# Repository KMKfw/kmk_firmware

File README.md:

# KMK: Clackety Keyboards Powered by Python

KMK is a feature-rich and beginner-friendly firmware for computer keyboards
written and configured in
[CircuitPython](https://github.com/adafruit/circuitpython).

## Status

KMK is no longer actively maintained and on limited life support.
Issues and pull requests will not be addressed for the time being.
Volunteers for taking on the project can voice their interest in the
[Zulip Chat](https://kmkfw.zulipchat.com).

## Support

For asynchronous support and chatter about KMK, [join our Zulip
community](https://kmkfw.zulipchat.com)!

If you ask for help in chat or open a bug report, if possible
make sure your copy of KMK is up-to-date.
In particular, swing by the Zulip chat *before* opening a GitHub Issue about
configuration, documentation, etc. concerns.

> The former Matrix and Discord rooms once linked to in this README are no
> longer officially supported, please do not use them!

## Features

- Fully configured through a single, easy to understand Python file that lives
  on a "flash-drive"-esque space on your microcontroller - edit on the go
  without DFU or other dev tooling available!
- Single-piece or [two-piece split
  keyboards](/docs/en/split_keyboards.md)
  are supported
- [Chainable
  keys](/docs/en/keys.md) such as
  `KC.LWIN(KC.L)` to lock the screen on a Windows PC
- [Built-in Unicode macros, including
  emojis](/docs/en/macros.md)
- [RGB underglow](/docs/en/rgb.md)
  and [LED
  backlights](/docs/en/led.md)
- One key can turn into many more based on [how many times you tap
  it](/docs/en/tapdance.md)
- Bluetooth HID and split keyboards. No more wires.

## Getting Started

KMK requires [CircuitPython](https://circuitpython.org/) version 8.0 or higher.
Our getting started guide can be found
[here](/docs/en/Getting_Started.md).

## Contributing

Please have a look at the [contributing document](/docs/en/contributing.md), 
where you can find details about the workflow and code style. If you have 
specific questions feel free to ask in the [KMK development stream](https://kmkfw.zulipchat.com/#narrow/stream/384078-KMK-development) 
on Zulip.

## License, Copyright, and Legal

All software in this repository is licensed under the [GNU Public License,
version 3](https://tldrlegal.com/license/gnu-general-public-license-v3-(gpl-3)).
All documentation and hardware designs are licensed under the [Creative Commons
Attribution-ShareAlike 4.0](https://creativecommons.org/licenses/by-sa/4.0/)
license.

**Due to ethical and legal concerns, any works derived from GitHub Copilot or
similar artificial intelligence tooling are unacceptable for inclusion in any
first-party KMK repository or other code collection. We further recommend not
using GitHub Copilot while developing anything KMK-related, regardless of
intent to submit upstream.**

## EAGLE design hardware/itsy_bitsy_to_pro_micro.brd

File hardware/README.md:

# KMK Hardware: Devices for use with KMK

## ItsyBitsy to Pro Micro pinout adapter

This board adapts the pinout of a Circuit Python compatible [Adafruit ItsyBitsy M4 Express](https://www.adafruit.com/product/3800) to that of the [SparkFun Pro Micro](https://www.sparkfun.com/products/12640) to allow the ItsyBitsy to be used with the many keyboards that support the footprint of the Pro Micro.

## Pin mapping
| Pro Micro Pin   | ItsyBitsy Pin   |
|-----------------|-----------------|
| `TX0/PD3`       | `TX`            |
| `RX1/PD2`       | `RX`            |
| `GND`           | `GND`           |
| `GND`           | `GND`           |
| `2/PD1`         | `SDA`           |
| `3/PD0`         | `SCL`           |
| `4/PD4`         | `D13`           |
| `5/PC6`         | `D12`           |
| `6/PD7`         | `D11`           |
| `7/PE6`         | `D10`           |
| `8/PB4`         | `D9`            |
| `9/PB5`         | `D7`            |
| `Raw`           |                 |
| `GND`           | `GND`           |
| `RST`           | `RST`           |
| `VCC`           | `USB`           |
| `A3/PF4`        | `A0`            |
| `A2/PF5`        | `A1`            |
| `A1/PF6`        | `A2`            |
| `A0/PF7`        | `A3`            |
| `15/PB1`        | `A4`            |
| `14/PB3`        | `A5`            |
| `16/PB2`        | `SCK`           |

## So how do I use it?
1. The pads for the Pro Micro footprint are circled on the underside of the board. Solder male headers into these pads on the underside of the board (the same side as the markings) so that the pins extend "downward" so that they can be plugged into the keyboard.

2. The remaining pads are for the ItsyBitsy. Assuming height is a concern, rather than soldering male headers into the ItsyBitsy and female headers into the adapter board, instead place the long side of male headers through the ItsyBitsy pads from underneath the board so that they protrude through he pads on the top of the board and solder them in place. Make sure to keep the headers perpendicular to the surface of the board.

3. Once soldered, place the ItsyBitsy board over the headers that are now protruding upwards so that the headers go through the pads of the ItsyBitsy and solder in place.

4. Trim the ItsyBitsy headers as needed with flush cutters.

## License, Copyright, and Legal

The files in this directory are licensed 
[CC BY-SA 4.0](https://tldrlegal.com/license/creative-commons-attribution-sharealike-4.0-international-(cc-by-sa-4.0))
while the TL;DR is linked, the full license text is included in `LICENSE.md` in this directory.

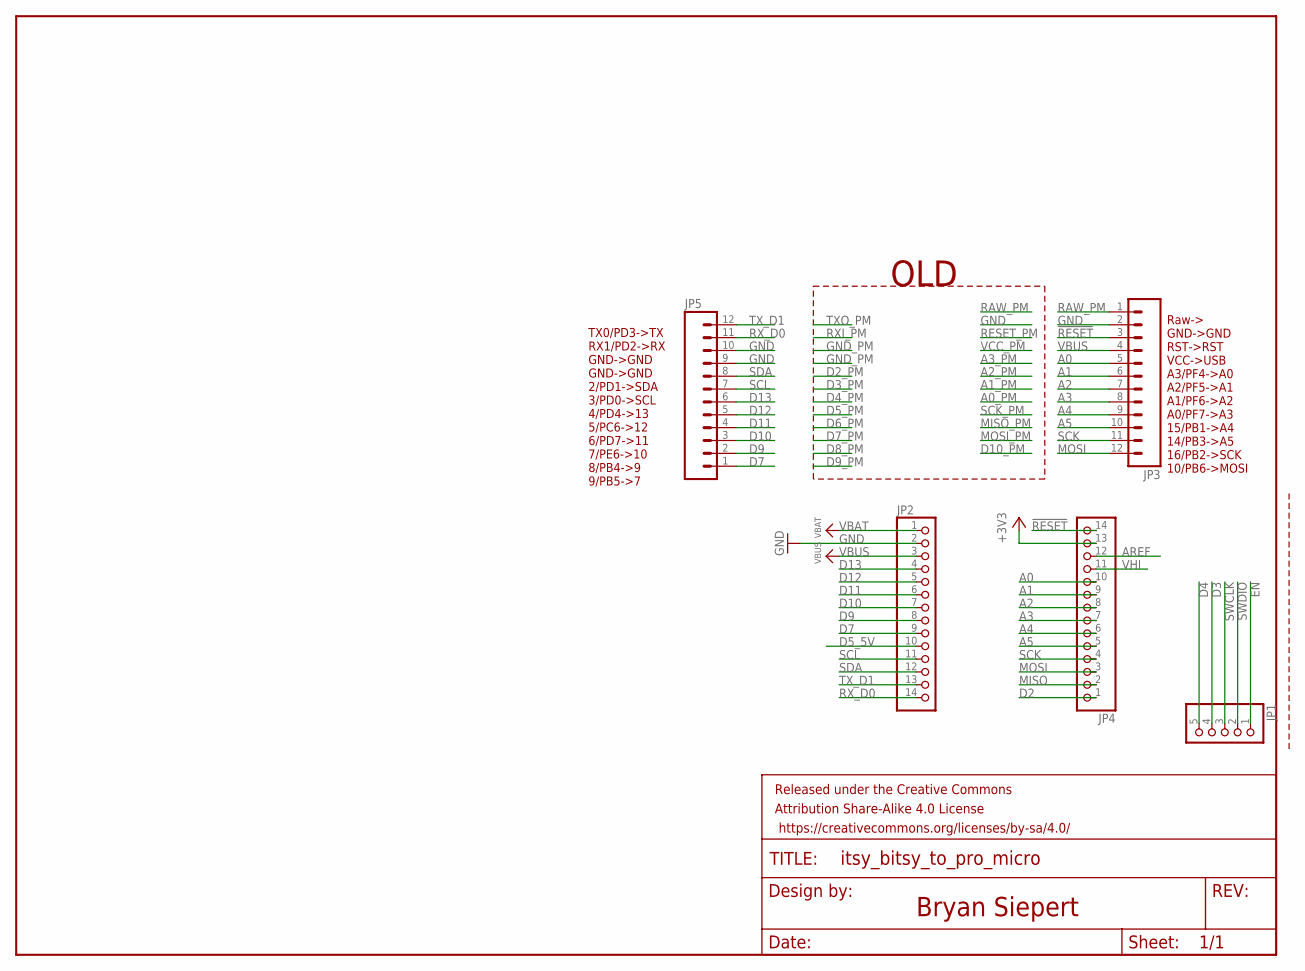
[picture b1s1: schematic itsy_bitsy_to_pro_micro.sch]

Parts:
FRAME2: FRAME-LETTER; CREATIVE_COMMONS
JP1: HEADER-1X570MIL; 1X05_ROUND_70
JP2, JP4: HEADER-1X14; 1X14_ROUND70
JP3, JP5: M12PTH; 1X12

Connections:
!RESET: JP3.3, JP4.14
+3V3: JP4.13
A0: JP3.5, JP4.10
A1: JP3.6, JP4.9
A2: JP3.7, JP4.8
A3: JP3.8, JP4.7
A4: JP3.9, JP4.6
A5: JP3.10, JP4.5
AREF: JP4.12
D2: JP4.1
D3: JP1.4
D4: JP1.5
D5_5V: JP2.10
D7: JP2.9, JP5.1
D9: JP2.8, JP5.2
D10: JP2.7, JP5.3
D11: JP2.6, JP5.4
D12: JP2.5, JP5.5
D13: JP2.4, JP5.6
EN: JP1.1
GND: JP2.2, JP3.2, JP5.9, JP5.10
MISO: JP4.2
MOSI: JP3.12, JP4.3
RAW_PM: JP3.1
RX_D0: JP2.14, JP5.11
SCK: JP3.11, JP4.4
SCL: JP2.11, JP5.7
SDA: JP2.12, JP5.8
SWCLK: JP1.3
SWDIO: JP1.2
TX_D1: JP2.13, JP5.12
VBAT: JP2.1
VBUS: JP2.3, JP3.4
VHI: JP4.11

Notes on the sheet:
TX0/PD3->TX RX1/PD2->RX GND->GND GND->GND 2/PD1->SDA 3/PD0->SCL 4/PD4->13 5/PC6->12 6/PD7->11 7/PE6->10 8/PB4->9 9/PB5->7
OLD
Raw-> GND->GND RST->RST VCC->USB A3/PF4->A0 A2/PF5->A1 A1/PF6->A2 A0/PF7->A3 15/PB1->A4 14/PB3->A5 16/PB2->SCK 10/PB6->MOSI
Bryan Siepert

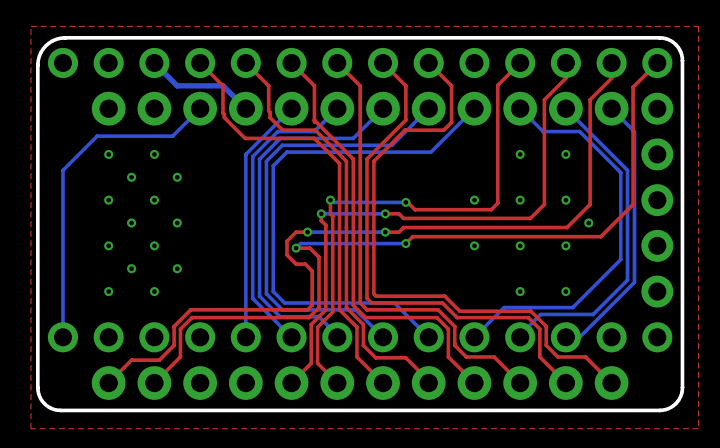
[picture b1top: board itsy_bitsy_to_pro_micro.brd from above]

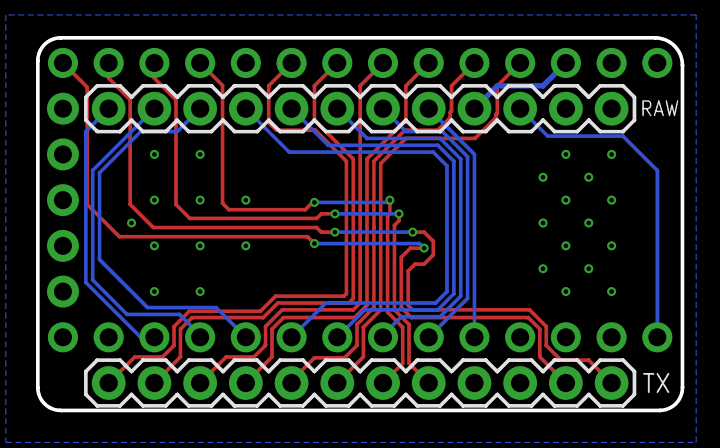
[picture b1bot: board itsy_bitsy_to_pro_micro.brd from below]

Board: 2 copper layers, 35.8 x 20.7 mm, 6 parts (2 on the bottom side), 21 nets.

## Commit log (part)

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2024-07-26 Update pimoroni_trackball.py
    Change variable names
2024-07-29 Fix runtime removal of failed extensions
2024-07-31 removed duplicate newline
2024-07-31 line length linting
2024-08-15 Fix kana check in lock_status.py
2024-08-15 Fix typo in combo_layers.md (#1017)
    changes KC.8 to KC.N8
    fixes a minor typo in the example
2024-08-20 Add docs for pimoroni trackball handlers (#1020)
2024-08-28 Fixed grammatical mistakes, added clarification (#1022)
    When I first wrote this doc, I made a ton of mistakes. Came back to it to clean it up a bit and it should make more sense now.
2024-08-31 Fix formatting
    make black happy
2024-08-31 Fix spelling in oneshot.md
2024-09-03 Refactor RapidFire
    * Fix RapidFireKey argument expansion
    * Add basic unit test
    * Fix calling keyboard.tap() from within a scheduled task
    * Simplify code and memory management
2024-09-03 Fix dependency of TapDance on instantiated HoldTap
2024-09-19 International keys didn't work (#1029)
    * Update international.py
    Fixes the International Keys
    ---------
2024-09-20 Use includes instead of excludes for black
2024-09-23 Keep spellcheck from searching hidden directories.
    Otherwise spellcheck will search for example in `.venv` for typos in
    tooling packages. Maybe the search expression should be a positive list.
2024-10-08 Refactor venv (#1031)
    * Merge setup.cfg into pyproject.toml
    * Use includes instead of excludes for black
    * Remove pipenv dependency
    * Keep spellcheck from searching hidden directories.
    Otherwise spellcheck will search for example in `.venv` for typos in
    tooling packages. Maybe the search expression should be a positive list.
2024-10-17 Add documentation for custom keys
2024-10-19 Fix an error in rgb.md
2024-10-21 Fix key class in international.py
2024-10-21 Fix key class in international.py (#1038)
    * Fix key class in international.py
    * fixup
2024-11-04 Minor tweaks to the example in the Display extension doc (#926)
    Minor tweaks to the Display extension doc
2024-11-04 flip layout (one handed typing)
2024-11-04 Removed intify_coordinate from code, boards, docs (#924)
    Remove deprecated intify_coordinate mapping
2024-11-04 Fix spelling (#920)
    Fix spelling
2024-11-04 undebug
2024-11-04 clean up (a little)
2024-11-04 minor doc updates
2024-11-05 Add TGS command to toggle between active layers
2024-11-07 Expose it in other scanners as well
2024-11-07 Even saner defaults
2024-11-07 Lint
2024-11-07 Lint III
2024-11-08 Catching all them arguments
2024-11-08 Allow passing debounce_threshold in keypad.py (#1044)
    * Expose debounce_threshold in keypad.py
2024-11-10 Add __init__() to KMKKeyboard
2024-11-19 Remove OneShot module
2024-11-19 Replace print() with guarded debug()
2024-11-19 Remove KC.DEBUG from keys.py
2024-11-19 Bring back DEBUG key
2024-12-09 Make bootcfg sense optional
    In case we're only interested in non-lockout-prone options, like NKRO
2024-12-09 remove `KC.DEBUG` cleanup
2024-12-10 Implement generalized analog input module
2024-12-11 Fix sticky_keys defer_release
2024-12-14 New unit tests
2024-12-14 Fix sticky_keys hold release (#1055)
    * Fix sticky_keys hold release
    * Update sticky_keys.md
    * Update aspell.en.pws
    * New unit tests
2024-12-15 Fixed and added to docs, changed senstol to sensitivity
    fixed AnalogKeys example, added sensitivity to docs and changed name in code from senstol (tolerance might be better wording not sure..)
    changed analog in examples to analogInputMap to better match up with keymap.py naming for encoders and what-not
    added explanation to AnalogKey example to better explain what it does
2024-12-16 Fix scanners.md
2024-12-16 Appease linter
2024-12-16 Fix scanners.md (#1058)
    * Fix scanners.md
    * Fix affected boards
2024-12-18 add start_watchdog() method
2024-12-18 better naming and neater debug
2024-12-22 remove artifacts
2024-12-23 Fix DiodeOrientation to columns_to_anodes mapping
2024-12-29 made analogio scanner (not mux yet)
    Made AnalogIo scanner that can scan single input.
    muxing should just be adding scanning with shifing the pins on the mux so not to hard but will need to take in muxers as an array in themself so multiple can be supported at once
    this is mostly baised on the Digital Io scanner but I see no exsamples as to where it gets it's offset from.
2024-12-29 changed threshold to threshold_map
    added parcing for a threshhold map and code to fill it with 127's of nothing provided
2025-01-03 boards/anavi/knob1/README.md: Display
    Add information about the Display extension for ANAVI Knob 1.
2025-01-04 boards/anavi/macro-pad-12/README.md: Fix link (#1065)
    Fix the link to the documentation for the display.
2025-01-06 larger rework
    the more I learn the more I "fix"
    this one is mainly wordy with my notes but I've moved a lot of handling out of update state and it only does that now
    also fixed update state still updating the value whitch allowed slower movement to get through
    added eval_filter to be an exteral function to invert the filter and get it's max (shoudl be renamed to invert_filter...)
    been thinking mainly about memory usage and have been trying to resuse it for when a larger keyboard comes along as the is currenly a lot stored by
    added velocity calc but it needs to run when called (to limit unessacary math as it uses divis)
2025-01-08 Fix ModifiedKey roll-interaction with non-modified keys
2025-01-08 Refactor hid.py
    * Small memory and performance improvements, mostly const() and bytearray
    ops.
    * Separate out report specific code into report classes. Serves as a base
    for easier addition of custom endpoints in "the future".
    * Lots of small integration changes, for example a simpler mechanism to
    record reports for unit tests (now with potential to verify other
2025-01-08 Fix custom hid pointer report
2025-01-08 Refactor hid.py (#1068)
    * Small memory and performance improvements, mostly const() and bytearray
    ops.
    * Separate out report specific code into report classes. Serves as a base
    for easier addition of custom endpoints in "the future".
    * Lots of small integration changes, for example a simpler mechanism to
    record reports for unit tests (now with potential to verify other
2025-01-10 ANAVI Knobs 3: Support SSD1306 I2C OLED Display (#1070)
    * boards/anavi/knobs3/code.py: Add display
    Add a new feature to support a mini OLED I2C SSD1306 display.
    * boards/anavi/knobs3/README.md: Display
    Add information about the Display extension for ANAVI Knobs 3.
    ---------
2025-01-27 Enable recursion for callables in macros
2025-01-31 Fix a mistake scanners.md (#1074)
2025-02-02 fix(KMKKeyboard)!: use __init__ to initialize the keyboard class
    KMKKeyboard has used class attributes instead of instance attributes.
    That is fundamentally incorrect, but hasn't caused issues in situ, where
    there's only ever one keyboard instance and the VM is reset with each
    restart.
    It does however cause issues in unit tests, where erroneous internal
    states can bleed over from failed tests to normally passing tests.
2025-02-03 fix(KMKKeyboard)!: use __init__ to initialize the keyboard class (#1077)
    KMKKeyboard has used class attributes instead of instance attributes.
    That is fundamentally incorrect, but hasn't caused issues in situ, where
    there's only ever one keyboard instance and the VM is reset with each
    restart.
    It does however cause issues in unit tests, where erroneous internal
    states can bleed over from failed tests to normally passing tests.
2025-02-03 fix(KMKKeyboard)!: use __init__ to initialize the keyboard class (2)
2025-02-11 docs(analogin): fix typo
2025-02-12 fix(analogin): fix evtmap memoization (#1082)
2025-02-13 refactor(analogin): remove extension-only methods
2025-02-14 Feature analogin: submodule + update scheduling (#1080)
    * feat(analogin): use a periodic background task for updating
    * refactor(analogin): remove extension-only methods
    * refactor(analogin): split components into submodule
2025-02-17 fix AC Pan descriptor
2025-02-18 initial hid.py modification
2025-02-18 add class SixAxis. Getting debug spam on keypress.
2025-02-19 fix formatting
2025-02-19 usb_args for set_usb_id
2025-02-20 modified Report ID descriptors for mouse and consumer
2025-02-20 remove clamp from SixAxisDeviceReport super().__init__()
2025-02-20 append six_axis last to fix unexpectedly large scroll
2025-02-20 fix report_id ValueError
2025-02-20 fix(combo): emit result to processing pipeline
    This is necessary in order for other processing modules (sticky keys,
    holdtap, etc.) to see the combo result as a "regular" key event.
2025-02-20 Add doc entry, SX -> SM (SpaceMouse) and ABC rotational axes to match CNC convention.
2025-02-20 remove whitespace
2025-02-21 button report
2025-02-21 modify six_axis description
2025-02-26 doc: change dead links from kmkfw.io to repo docs (#1089)
2025-03-04 fix a typo for ble connected check (#1090)
2025-03-04 Fix warning box
2025-03-08 SpacemouseStatus extension and documentation
2025-03-08 Add SpacemouseStatus
2025-03-08 limit move_step to max_speed
2025-03-09 Implement Six Axis HID
2025-03-10 Fix formattning
2025-03-10 Fix more formatting and warnings
2025-03-11 test: fix spellcheck (#1096)
2025-03-11 use len() instead of hasattr()
2025-03-12 15ms timestep to prevent high deltas waiting to be sent
2025-03-17 Update README.md
    fix #1097
2025-03-17 move IdentifiedDevice
2025-03-17 Update README.md (#1098)
2025-03-26 feat(bootcfg): set usb identification with a kwargs-dict (#1100)
2025-04-02 class SpacemouseDirectionKey
2025-04-02 remove unneeded mask checks
2025-04-02 Refactor mouse_keys to use MouseDirectionKey. Tuple for setting mouse and wheel timestep.
2025-04-10 Add C64 Badge
2025-04-15 SpacemouseKeys module (#1093)
    * SpacemouseKeys module and documentation
    * Add Spacemouse Keys
    * Rename acc_interval to timestep_ms. Reset _move_step to 0.
    * 15ms timestep to prevent high deltas waiting to be sent
    * Use class SpacemouseDirectionKey. Remove reduntant _movement masks.
    * refactor(spacemouse_keys): flatten _on_press call
2025-04-15 fix capitalisation
2025-04-15 Tag markdown block as Python in mouse_jiggler.md
2025-04-16 Fix lint.
2025-04-22 docs: fix spelling (#1106)
2025-04-26 isort lint
2025-04-27 SpacemouseStatus extension (#1094)
    * SpacemouseStatus extension and documentation
2025-05-12 added the media_keys extension import in encoder.md example
    the example provided in the encoder.md uses media_keys extension but the extension is not imported or appended
2025-05-15 feat!: change task queue interface to accomodate CP 10
    BREAKING CHANGE:
    This will break compatibility with CircuitPython version < 9.
2025-06-05 Cp10 (#1111)
    * feat!: change task queue interface to accomodate CP 10
    BREAKING CHANGE:
    This will break compatibility with CircuitPython version < 9.
    * docs: bump required CP version to 8.0
2025-07-05 Re-run isort and formatting
2025-07-15 fix: fix steno keys
2025-07-18 Fix BKDL and GESC
2025-07-18 Fix tests
2025-07-19 first try
2025-09-16 fix: fix `StenoKey` parent class
2025-09-30 Add UK layout
2025-10-01 Add UK layout support to Psion keyboard (#1124)
2025-10-03 Update README.md
    Mention UK layout support
2025-10-03 Add extra blank row to keep black happy
2025-12-20 Gobble kwargs to prevent unexpected keyword arg error when defining a ble_name and switching HID modes
2026-01-17 Switch to i2cdisplaybus.I2CDisplayBus
2026-02-04 Update scanners.md
    Bring scanners examples in line with expected usage
2026-02-06 Update scanners.md (#1131)
    * Update scanners.md
    Bring scanners examples in line with expected usage
    * Match variable names to argument names
    ---------
2026-02-14 added arg and property for `add_buttons: int` for adding singleton/single-pin buttons to the `coord_mapping`, rather than the user needing to create the coord_mapping manually.
2026-02-14 added an update to the `split_offset` to reduce the up-front code when using `add_buttons`
2026-02-14 updated RotaryioEncoder section of scanners.md to have better example code.
2026-02-14 added documentation for the `add_buttons` argument
2026-02-19 removed debug.enabled line, left two empty lines for linter
2026-02-19 ran black formatter
2026-02-19 Adding Easier Configuration for Dual-Side Encoders On Split Keyboards (#1133)
    * added arg and property for `add_buttons: int` for adding singleton/single-pin buttons to the `coord_mapping`, rather than the user needing to create the coord_mapping manually.
    * added documentation for the `add_buttons` argument
    * updated description for Multiple Scanners with Custom `coord_mapping`
2026-02-19 fix spelling: scanners.md
2026-03-08 ANAVI Knobs 3: Fix when running without a display
    Handle runtime error if mini I2C OLED display has not been attached
    to ANAVI Knobs 3. Fixes:
    RuntimeError: No pull up found on SDA or SCL; check your wiring
2026-03-22 Add DuplexMatrixScanner documentation.
2026-03-23 Tipo while importing DuplexMatrixScanner in scanners.md
2026-03-24 Refactor DuplexMatrixScanner
2026-04-09 Fix format and spelling.

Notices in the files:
parts and their libraries:
microbuilder: This work is placed in the public domain, and may be freely used for commercial and non-commercial work with the following conditions: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
SparkFun-Aesthetics: Licensing: Creative Commons ShareAlike 4.0 International - https://creativecommons.org/licenses/by-sa/4.0
